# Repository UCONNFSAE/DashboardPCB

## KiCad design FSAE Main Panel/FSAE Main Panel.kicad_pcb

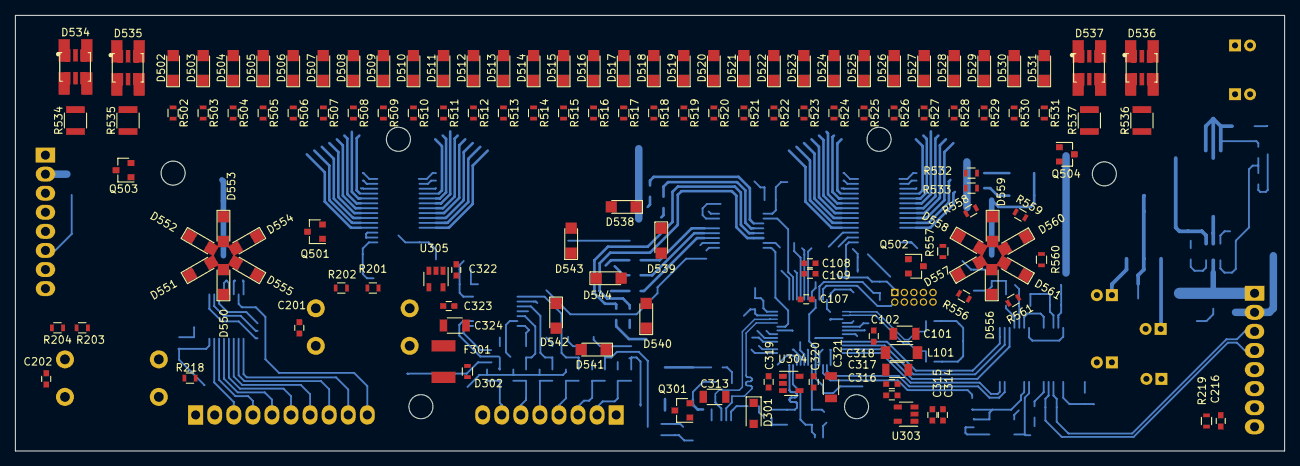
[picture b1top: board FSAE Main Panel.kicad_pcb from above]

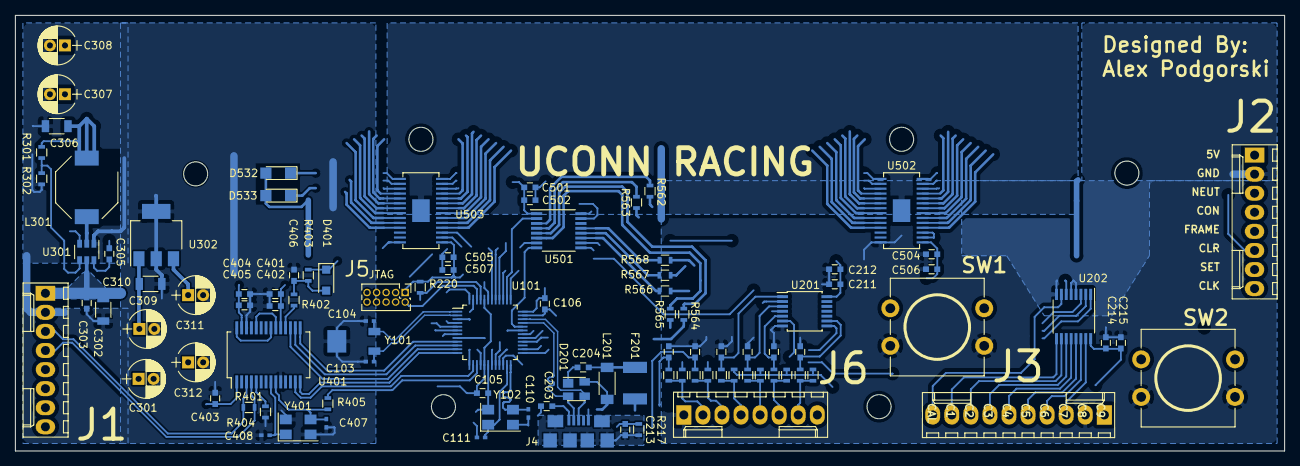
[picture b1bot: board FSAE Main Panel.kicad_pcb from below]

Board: 4 copper layers, 169.0 x 58.0 mm, 232 parts (99 on the bottom side), 183 nets.

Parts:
C101, C313, C318, C321, C324: 10uF; C_1206
C102, C105, C106, C107, C108, C205, C206, C207, C208, C209, C210, C211, C214, C305, C315, C316, C402, C403, C405, C406, C502, C504, C505: 0.1uF; C_0603
C103, C104, C110, C111, C407, C408: 9.1pF; C_0402_NoSilk
C109, C201, C202, C212, C215, C314, C317, C319, C320, C322, C323, C401, C404, C501, C506, C507: 1uF; C_0603
C203, C204, C213, C216, C303: 4700pF; C_0603
C301, C307, C309, C311: 22uF; CP_Radial_D5.0mm_P2.00mm
C302, C306, C310: 2.2uF; C_1206
C308, C312: 100uF; CP_Radial_D5.0mm_P2.00mm
D201: PRTR5V0U2X; SOT-143
D301, D401: D; D_SOD-123F
D302: D_TVS; R_0603
D502, D503, D504, D505, D506, D507, D508, D509, D510, D511, D512, D513, D514, D515, D516, D517: SM1206NPGC-IL; LED_1206
D518, D519, D520, D521, D522, D523, D524, D525, D550, D551, D552, D553, D554, D555: SM1206NYC-IL; LED_1206
D526, D527, D528, D529, D530, D531, D532, D533, D556, D557, D558, D559, D560, D561: SM1206NHC-IL; LED_1206
D534, D535, D536, D537: LCB G6SP-DBFA-4J5L-0-140-R18-Z; LCB_G6SP
D538, D539, D540, D541, D542, D543, D544: SM1206NUWC-IL; LED_1206
F201, F301: MF-MSMF050-2
J1, J2, J6: Conn_01x08; Molex_KK-6410-08_08x2.54mm_Straight
J3: Conn_01x10; Molex_KK-6410-10_10x2.54mm_Straight
J4: USB Micro B; 10118192-0001LF
J5: Cortex_Debug; Pin_Header_Straight_2x05_Pitch1.27mm
L101, L201: BLM41PG471SN1L; L_1806
L301: 3.3uH; L_Bourns-SRU8043
Q301: DMG2305UX-13; SOT-23
Q501, Q502, Q503, Q504: SI2308CDS-T1-GE3; SOT-23
R201, R203, R205, R207, R209, R211, R213, R215, R218, R302, R403, R404: 10k; R_0603
R202, R204, R206, R208, R210, R212, R214, R216: 330; R_0603
R217, R219: 1M; R_0603
R220, R402: 1k; R_0603
R301: 56.2k; R_0603
R401, R502, R503, R504, R505, R506, R507, R508, R509, R510, R511, R512, R513, R514, R515, R516, R517, R518, R519, R520, R521, R522, R523, R524, R525, R526, R527, R528, R529, R530, R531, R532, R533, R556, R557, R558, R559, R560, R561, R562, R563, R564, R565, R566, R567, R568: 120; R_0603
R405: 0; R_0603
R534, R535, R536, R537: 11; R_1210
SW1, SW2: SW_SPST; PTS125
U101: SAMD21G18A-AU; TQFP-48_7x7mm_Pitch0.5mm
U201: CD40106BPWR; TSSOP-14_4.4x5mm_Pitch0.65mm
U202: CD74HC238PWR; TSSOP-16_4.4x5mm_Pitch0.65mm
U301: TPS564201; SOT-23-6
U302: LM2940IMP-5.0/NOPB; SOT-223-3_TabPin2
U303, U304, U305: LP5907MFX-3.3; SOT-23-5
U401: MCP25625; SSOP-28_5.3x10.2mm_Pitch0.65mm
U501: TLC6C598; TSSOP-16_4.4x5mm_Pitch0.65mm
U502, U503: TLC6C5816
Y101: 32.768kHz; MS1V-T1K
Y102, Y401: 16MHz; Crystal_SMD_5032-4pin_5.0x3.2mm

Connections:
+3.3VA: C105.2, C107.1, C316.1, C317.1, C318.1, L101.2, U101.17, U101.44, U303.5
+3V3: C106.1, C211.1, C212.1, C320.1, C321.1, C401.1, C402.1, C403.1, C501.1, C502.1, C504.2, C505.2, C506.1, C507.1, D401.1, J5.1, R201.1, R203.1, R220.1, R403.1, U101.36, U201.14, U202.6, U304.5, U401.1, U401.19, U501.1, U502.1, U503.1
+5V: C311.1, C312.1, C404.1, C405.1, D301.2, Q301.1, U302.3, U401.27
/CAN/X16M_C+: C407.1, R405.1, U401.9, Y401.3
/CAN/X16M_C-: C408.1, U401.8, Y401.1
/Display/B1: D534.1, R534.2
/Display/B2: D535.1, R535.2
/Display/B3: D536.1, R536.2
/Display/B4: D537.1, R537.2
/Display/FRAME_INT1: U501.9, U503.12
/Display/FRAME_INT2: U502.12, U503.15
/Display/G1: D502.1, R502.1
/Display/G2: D503.1, R503.1
/Display/G3: D504.1, R504.1
/Display/G4: D505.1, R505.1
/Display/G5: D506.1, R506.1
/Display/G6: D507.1, R507.1
/Display/G7: D508.1, R508.1
/Display/G8: D509.1, R509.1
/Display/G9: D510.1, R510.1
/Display/G10: D511.1, R511.1
/Display/G11: D512.1, R512.1
/Display/G12: D513.1, R513.1
/Display/G13: D514.1, R514.1
/Display/G14: D515.1, R515.1
/Display/G15: D516.1, R516.1
/Display/G16: D517.1, R517.1
/Display/OP1: D556.1, R556.1
/Display/OP2: D557.1, R557.1
/Display/OP3: D558.1, R558.1
/Display/OP4: D559.1, R559.1
/Display/OP5: D560.1, R560.1
/Display/OP6: D561.1, R561.1
/Display/OP_CONTROL: Q502.3, R556.2, R557.2, R558.2, R559.2, R560.2, R561.2
/Display/R1: D526.1, R526.1
/Display/R2: D527.1, R527.1
/Display/R3: D528.1, R528.1
/Display/R4: D529.1, R529.1
/Display/R5: D530.1, R530.1
/Display/R6: D531.1, R531.1
/Display/R7: D532.1, R532.1
/Display/R8: D533.1, R533.1
/Display/RPM_1: R502.2, U502.4
/Display/RPM_2: R503.2, U502.5
/Display/RPM_3: R504.2, U502.6
/Display/RPM_4: R505.2, U502.7
/Display/RPM_5: R506.2, U502.8
/Display/RPM_6: R507.2, U502.9
/Display/RPM_7: R508.2, U502.10
/Display/RPM_8: R509.2, U502.11
/Display/RPM_9: R510.2, U502.18
/Display/RPM_10: R511.2, U502.19
/Display/RPM_11: R512.2, U502.20
/Display/RPM_12: R513.2, U502.21
/Display/RPM_13: R514.2, U502.22
/Display/RPM_14: R515.2, U502.23
/Display/RPM_15: R516.2, U502.24
/Display/RPM_16: R517.2, U502.25
/Display/RPM_17: R518.2, U503.4
/Display/RPM_18: R519.2, U503.5
/Display/RPM_19: R520.2, U503.6
/Display/RPM_20: R521.2, U503.7
/Display/RPM_21: R522.2, U503.8
/Display/RPM_22: R523.2, U503.9
/Display/RPM_23: R524.2, U503.10
/Display/RPM_24: R525.2, U503.11
/Display/RPM_25: R526.2, U503.18
/Display/RPM_26: R527.2, U503.19
/Display/RPM_27: R528.2, U503.20
/Display/RPM_28: R529.2, U503.21
/Display/RPM_29: R530.2, U503.22
/Display/RPM_30: R531.2, U503.23
/Display/RPM_31: R532.2, U503.24
/Display/RPM_32: R533.2, U503.25
/Display/SFT_1: Q504.3, R536.1, R537.1
/Display/SFT_2: Q503.3, R534.1, R535.1
/Display/Y1: D518.1, R518.1
/Display/Y2: D519.1, R519.1
/Display/Y3: D520.1, R520.1
/Display/Y4: D521.1, R521.1
/Display/Y5: D522.1, R522.1
/Display/Y6: D523.1, R523.1
/Display/Y7: D524.1, R524.1
/Display/Y8: D525.1, R525.1
/Display/a: D538.1, R562.1
/Display/aI: R562.2, U501.3
/Display/b: D539.1, R563.1
/Display/bI: R563.2, U501.4
/Display/c: D540.1, R564.1
/Display/cI: R564.2, U501.5
/Display/d: D541.1, R565.1
/Display/dI: R565.2, U501.6
/Display/e: D542.1, R566.1
/Display/eI: R566.2, U501.11
/Display/f: D543.1, R567.1
/Display/fI: R567.2, U501.12
/Display/g: D544.1, R568.1
/Display/gI: R568.2, U501.13
/External Interface/CAL2: J3.3, U202.15
/External Interface/CAL3: J3.4, U202.14
/External Interface/CAL4: J3.5, U202.13
/External Interface/CAL5: J3.6, U202.12
/External Interface/CAL6: J3.7, U202.11
/External Interface/CAL7: J3.8, U202.10
/External Interface/CAL8: J3.9, U202.9
/External Interface/CAL9: J3.10, U202.7
/External Interface/CAN_SHLD: C216.2, J1.8, R219.1
/External Interface/DSFT_a: J6.3, R207.1, R208.1
/External Interface/SW1_L: C201.1, R202.2, SW1.2
/External Interface/SW2_L: C202.1, R204.2, SW2.2
/External Interface/SWS1_a: J6.4, R209.1, R210.1
/External Interface/SWS1_d: C207.1, R210.2, U201.1
/External Interface/SWS2_a: J6.5, R211.1, R212.1
/External Interface/SWS2_d: C208.1, R212.2, U201.3
/External Interface/SWS3_a: J6.6, R213.1, R214.1
/External Interface/SWS3_d: C209.1, R214.2, U201.5
/External Interface/SWS4_a: J6.7, R215.1, R216.1
/External Interface/SWS4_d: C210.1, R216.2, U201.9
/External Interface/USB_SHLD: C213.1, J4.6, R217.2
/External Interface/USFT_a: J6.2, R205.1, R206.1
/External Interface/VBUS: C203.2, D201.4, J4.1, L201.2
/External Interface/V_USB_1: C204.2, F201.2, L201.1
/Power/+5V_INT: C313.1, C314.1, C315.1, C319.1, C322.1, D301.1, Q301.2, U303.1, U303.3, U304.1, U304.3, U305.1, U305.3
/VCORE1: C108.1, C109.1, U101.43
/VDDANA: C101.1, C102.1, L101.1, U101.6
/X16M+: C111.1, U101.23, Y102.1
/X16M-: C110.1, U101.24, Y102.3
/X32+: C104.2, U101.1, Y101.1
/X32-: C103.2, U101.2, Y101.2
CAL_IN: J3.1, R218.1, U101.22
CAL_a: U101.28, U202.1
CAL_b: U101.29, U202.2
CAL_c: U101.30, U202.3
CAN_CS: U101.11, U401.17
CAN_IN+: J1.4, R401.2, U401.4
CAN_IN-: J1.3, R401.1, U401.3
CAN_INT: U101.14, U401.13
CAN_MISO: U101.10, U401.16
CAN_MOSI: U101.9, U401.15
CAN_SCLK: U101.12, U401.14
CAN_V+: C301.1, C302.1, C303.1, C309.1, C310.1, J1.1, R205.2, R207.2, U301.3, U301.5, U302.1
DSFT: C206.1, J1.6, R208.2
DWC_CONT: J2.4, U101.8
EXT_+3V3: C214.1, C215.1, D302.1, F301.1, R209.2, R211.2, R213.2, R215.2, U202.16
FRAME_CLK: J2.8, U101.37, U501.15, U502.17, U503.17
FRAME_CLR: J2.6, U101.48, U501.7, U502.13, U503.13
FRAME_IN: U101.38, U501.2
FRAME_OUT: J2.5, U502.15
FRAME_SET: J2.7, U101.41, U501.10, U502.16, U503.16
GCLK_0: R405.2, U101.15
GND: C101.2, C102.2, C103.1, C104.1, C105.1, C106.2, C107.2, C108.2, C109.2, C110.2, C111.2, C201.2, C202.2, C203.1, C204.1, C205.2, C206.2, C207.2, C208.2, C209.2, C210.2, C211.2, C212.2, C213.2, C214.2, C215.2, C216.1, C301.2, C302.2, C303.2, C306.2, C307.2, C308.2, C309.2, C310.2, C311.2, C312.2, C313.2, C314.2, C315.2, C316.2, C317.2, C318.2, C319.2, C320.2, C321.2, C322.2, C323.2, C324.2, C401.2, C402.2, C403.2, C404.2, C405.2, C406.2, C407.2, C408.2, C501.2, C502.2, C504.1, C505.1, C506.2, C507.2, D201.1, D302.2, J1.2, J2.2, J3.2, J4.5, J5.3, J5.5, J6.1, Q501.2, Q502.2, Q503.2, Q504.2, R217.1, R218.2, R219.2, R302.2, R404.2, SW1.1, SW2.1, U101.5, U101.18, U101.35, U101.42, U201.7, U202.4, U202.5, U202.8, U301.1, U302.2, U303.2, U304.2, U305.2, U401.10, U401.26, U501.16, U502.28, U503.28, Y101.3, Y102.2, Y102.4, Y401.2, Y401.4
HIGH_TEMP: Q501.1, U101.39
LED_+5V: C306.1, C307.1, C308.1, D502.2, D503.2, D504.2, D505.2, D506.2, D507.2, D508.2, D509.2, D510.2, D511.2, D512.2, D513.2, D514.2, D515.2, D516.2, D517.2, D518.2, D519.2, D520.2, D521.2, D522.2, D523.2, D524.2, D525.2, D526.2, D527.2, D528.2, D529.2, D530.2, D531.2, D532.2, D533.2, D534.2, D535.2, D536.2, D537.2, D538.2, D539.2, D540.2, D541.2, D542.2, D543.2, D544.2, D550.2, D551.2, D552.2, D553.2, D554.2, D555.2, D556.2, D557.2, D558.2, D559.2, D560.2, D561.2, J2.1, L301.1, R301.1
unnamed: C305.1, L301.2, U301.2
unnamed: C305.2, U301.6
unnamed: C323.1, C324.1, F301.2, U305.5
unnamed: C406.1, D401.2, R402.1, R403.2
unnamed: R301.2, R302.1, U301.4
unnamed: R402.2, U401.18
unnamed: R404.1, U401.5
unnamed: U401.20, U401.24
unnamed: U401.21, U401.28
OIL_PRES: Q502.1, U101.7
SHIFT1: Q503.1, U101.3
SHIFT2: Q504.1, U101.4
SWCLK: J5.4, R220.2, U101.45
SWDIO: J5.2, U101.46
SWS1: U101.26, U201.2
SWS2: U101.25, U201.4
SWS3: U101.20, U201.6
SWS4: U101.21, U201.8
USB_D+: D201.3, J4.3, U101.34
USB_D-: D201.2, J4.2, U101.33
USB_POWER: F201.1, Q301.3
USFT: C205.1, J1.5, R206.2
~CLEAR: R203.2, R204.1, U101.19
~NEUT: J1.7, J2.3
~PWM_GREEN: U101.31, U502.2, U502.3
~PWM_RED: U101.16, U503.3
~PWM_WHITE: U101.32, U501.8
~PWM_YELLOW: U101.13, U503.2
~RESET: J5.10, R201.2, R202.1, U101.40
~RPM_EN: U101.47, U502.14, U503.14

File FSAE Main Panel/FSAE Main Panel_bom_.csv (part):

Component,Description,Part,References,Value,Footprint,Quantity Per PCB,Datasheet,Part Number,Sheetpath,Digikey P/N,Manufacturer,Function
1,"Unpolarized capacitor, small symbol",C_Small,C103 C104 C110 C111 C407 C408,9.1pF,C_0402_NoSilk,6,https://api.kemet.com/component-edge/download/datasheet/C040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,C0402C919C5GAC7867,/,399-14287-1-ND,KEMET,
2,Unpolarized capacitor,C,C203 C204 C213 C216 C303,4700pF,C_0603,5,https://api.kemet.com/component-edge/download/specsheet/C060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,C0603C472K5RACAUTO,/External Interface/,399-6896-1-ND,KEMET,
3,"Unpolarized capacitor, small symbol",C_Small,C102 C105 C106 C107 C108 C205 C206 C207 C208 C209 C210 C211 C214 C305 C315 C316 C402 C403 C405 C406 C502 C504 C505,0.1uF,C_0603,23,https://api.kemet.com/component-edge/download/specsheet/C060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,C0603C104K5RACAUTO,/,399-6856-1-ND,KEMET,
4,"Unpolarized capacitor, small symbol",C_Small,C109 C201 C202 C212 C215 C314 C317 C319 C320 C322 C323 C401 C404 C501 C506 C507,1uF,C_0603,16,https://api.kemet.com/component-edge/download/specsheet/C060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,C0603C105K4RACAUTO,/,399-17704-1-ND,KEMET,
5,Unpolarized capacitor,C,C302 C306 C310,2.2uF,C_1206,3,https://api.kemet.com/component-edge/download/specsheet/C120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,C1206C225K5RACAUTO,/Power/,399-7019-1-ND,KEMET,
6,"Unpolarized capacitor, small symbol",C_Small,C101 C313 C318 C321 C324,10uF,C_1206,5,https://api.kemet.com/component-edge/download/datasheet/C120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,C1206C106K4RACAUTO,/,399-7012-1-ND,KEMET,CAP CER 10UF 25V X5R 1206
7,Unpolarized capacitor,C,C301 C307 C309 C311,22uF,CP_Radial_D5.0mm_P2.00mm,4,https://api.kemet.com/component-edge/download/specsheet/ESK2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,ESK226M050AC3AA,/Power/,399-6108-ND,KEMET,
8,Unpolarized capacitor,C,C308 C312,100uF,CP_Radial_D5.0mm_P2.00mm,2,https://api.kemet.com/component-edge/download/datasheet/ESK1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,ESK107M016AC3AA,/Power/,399-6601-ND,KEMET,
9,Diode,D,D301 D401,D,D_SOD-123F,2,https://www.diodes.com/assets/Datasheets/MBR230S1F.pdf,MBR230S1F-7,/Power/,MBR230S1F-7DICT-ND,Diodes Inc,
10,Bidirectional transient-voltage-suppression diode,D_TVS,D302,D_TVS,R_0603,1,https://www.ti.com/lit/ds/symlink/tpd1e10b06.pdf,TPD1E10B06DPYR,/Power/,296-30406-1-ND,TI,
11,"Light emitting diode, small symbol",LED_Small,D534 D535 D536 D537,LCB G6SP-DBFA-4J5L-0-140-R18-Z,LCB_G6SP,4,https://dammedia.osram.info/media/resource/hires/osram-dam-6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,LCB G6SP-DBFA-4J5L-0-140-R18-Z,/Display/,475-3674-1-ND,OSRAM,Shift_1 Shift_2 Shift_3 Shift_4
12,,PRTR5V0U2X,D201,PRTR5V0U2X,SOT-143,1,https://assets.nexperia.com/documents/data-sheet/PRTR5V0U2X.pdf,"PRTR5V0U2X,215",/External Interface/,1727-3884-1-ND,Nexperia,
13,"Light emitting diode, small symbol",LED_Small,D526 D527 D528 D529 D530 D531 D532 D533 D556 D557 D558 D559 D560 D561,SM1206NHC-IL,LED_1206,14,https://www.bivar.com/Portals/0/Products/SM1206NHC-IL.pdf,SM1206NHC-IL,/Display/,492-1944-1-ND,Bivar,12500-Red 13000-Red 13500-Red 14000-Red 14500-Red 15000-Red Spare-Red Oil Pressure
14,"Light emitting diode, small symbol",LED_Small,D502 D503 D504 D505 D506 D507 D508 D509 D510 D511 D512 D513 D514 D515 D516 D517,SM1206NPGC-IL,LED_1206,16,https://www.bivar.com/parts_content/Datasheets/SM1206NPGC-IL.pdf,SM1206NPGC-IL,/Display/,492-1945-1-ND,Bivar,500-Green 1000-Green 1500-Green 2000-Green 2500-Green 3000-Green 3500-Green 4000-Green 4500-Green 5000-Green 5500-Green 6000-Green 6500-Green 7000-Green 7500-Green 8000-Green
15,"Light emitting diode, small symbol",LED_Small,D538 D539 D540 D541 D542 D543 D544,SM1206NUWC-IL,LED_1206,7,https://www.bivar.com/parts_content/Datasheets/SM1206NUWC-IL.pdf,SM1206NUWC-IL,/Display/,492-1946-1-ND,Bivar,7Seg_A 7Seg_B 7Seg_C 7Seg_D 7Seg_E 7Seg_F 7Seg_G
16,"Light emitting diode, small symbol",LED_Small,D518 D519 D520 D521 D522 D523 D524 D525 D550 D551 D552 D553 D554 D555,SM1206NYC-IL,LED_1206,14,https://www.bivar.com/Files/Datasheets/SM1206NYC-IL.pdf,SM1206NYC-IL,/Display/,492-1947-1-ND,Bivar,8500-Yellow 9000-Yellow 9500-Yellow 10000-Yellow 10500-Yellow 11000-Yellow 11500-Yellow 12000-Yellow High Temp
17,"Resettable fuse, polymeric positive temperature coefficient",Polyfuse,F201 F301,MF-MSMF050-2,MF-MSMF050-2,2,https://www.bourns.com/docs/Product-Datasheets/mfmsmf.pdf,MF-MSMF050-2,/External Interface/,IRLML6402PBFCT-ND,Bourns,
18,"Heatsink with electrical connection, 1 pin",Heatsink_Pad,HS1 HS2,Heatsink_Pad,PinHeader_1x01_P2.54mm_Vertical,2,~,,/Display/,,,
19,"Generic connector, single row, 01x08, script generated (kicad-library-utils/schlib/autogen/connector/)",Conn_01x08,J1 J2 J6,Conn_01x08,Molex_KK-6410-08_08x2.54mm_Straight,3,"https://media.digikey.com/pdf/Data%20Sheets/Molex%20PDFs/171856,57_Brief.pdf",1718571008,/External Interface/,WM10303-ND,Molex,
20,"Generic connector, single row, 01x10, script generated (kicad-library-utils/schlib/autogen/connector/)",Conn_01x10,J3,Conn_01x10,Molex_KK-6410-10_10x2.54mm_Straight,1,"https://media.digikey.com/pdf/Data%20Sheets/Molex%20PDFs/171856,57_Brief.pdf",0022122104,/External Interface/,WM2719-ND,Molex,
21,,Cortex_Debug,J5,Cortex_Debug,Pin_Header_Straight_2x05_Pitch1.27mm,1,https://cdn.amphenol-icc.com/media/wysiwyg/files/drawing/200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,20021111-00010T4LF,/External Interface/,609-3712-ND,Amphenol,
22,,Conn_01x06-conn,J4,USB Micro B,10118192-0001LF,1,https://www.amphenol-icc.com/media/wysiwyg/files/drawing/101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,10118192-0001LF,/External Interface/,609-4613-1-ND,Amphenol,
23,Inductor,L,L301,3.3uH,L_Bourns-SRU8043,1,https://www.bourns.com/docs/Product-Datasheets/SRR1050A.pdf,SRR1050A-3R3Y,/Power/,SRR1050A-3R3YCT-ND,Bourns,
24,"Ferrite bead, small symbol",Ferrite_Bead_Small,L101,BLM41PG471SN1L,L_1806,1,https://www.murata.com/en-us/products/productdata/8796739862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,BLM41PG471SN1L,/,490-1060-1-ND,Murata,
25,Ferrite bead,Ferrite_Bead,L201,BLM41PG471SN1L,L_1806,1,https://www.murata.com/en-us/products/productdata/8796739862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,BLM41PG471SN1L,/External Interface/,490-1060-1-ND,Murata,
26,"P-MOSFET transistor, gate/source/drain",Q_PMOS_GSD,Q301,DMG2305UX-13,SOT-23,1,https://www.diodes.com/assets/Datasheets/DMG2305UX.pdf,DMG2305UX-13,/Power/,DMG2305UX-13DICT-ND,Diodes Inc,
27,"N-MOSFET transistor, gate/source/drain",Q_NMOS_GSD,Q501 Q502 Q503 Q504,SI2308CDS-T1-GE3,SOT-23,4,http://www.vishay.com/docs/77744/si2308cds.pdf,SI2308CDS-T1-GE3,/Display/,SI2308CDS-T1-GE3CT-ND,Vishay,
28,Resistor,R,R405,0,R_0603,1,https://www.seielect.com/catalog/sei-rmcf_rmcp.pdf,RMCF0603ZT0R00,/CAN/,RMCF0603ZT0R00CT-ND,Stackpole,
29,"Resistor, small symbol",R_Small,R534 R535 R536 R537,11,R_1210,4,http://www.vishay.com/docs/20035/dcrcwe3.pdf,CRCW121011R0FKEA,/Display/,541-11.0AACT-ND,Vishay,
30,Resistor,R,R401 R502 R503 R504 R505 R506 R507 R508 R509 R510 R511 R512 R513 R514 R515 R516 R517 R518 R519 R520 R521 R522 R523 R524 R525 R526 R527 R528 R529 R530 R531 R532 R533 R550 R551 R552 R553 R554 R555 R556 R557 R558 R559 R560 R561 R562 R563 R564 R565 R566 R567 R568,120,R_0603,52,https://www.seielect.com/catalog/sei-rmcf_rmcp.pdf,RMCF0603FT120R,/CAN/,RMCF0603FT120RCT-ND,Stackpole,
31,Resistor,R,R202 R204 R206 R208 R210 R212 R214 R216,330,R_0603,8,https://www.seielect.com/catalog/sei-rmcf_rmcp.pdf,RMCF0603JT330R,/External Interface/,RMCF0603JT330RCT-ND,Stackpole,
32,Resistor,R,R220 R402,1k,R_0603,2,https://www.seielect.com/catalog/sei-rmcf_rmcp.pdf,RMCF0603JT1K00,/External Interface/,RMCF0603JT1K00CT-ND,Stackpole,
33,Resistor,R,R201 R203 R205 R207 R209 R211 R213 R215 R218 R302 R403 R404,10k,R_0603,12,https://www.seielect.com/catalog/sei-rmcf_rmcp.pdf,RMCF0603JT10K0,/External Interface/,RMCF0603JT10K0CT-ND,Stackpole,
34,Resistor,R,R301,56.2k,R_0603,1,https://www.seielect.com/catalog/sei-rmcf_rmcp.pdf,RMCF0603FT56K2,/Power/,RMCF0603FT56K2CT-ND,Stackpole,
35,"Resistor, small symbol",R_Small,R217 R219,1M,R_0603,2,https://www.seielect.com/catalog/sei-rmcf_rmcp.pdf,RMCF0603JT1M00,/External Interface/,RMCF0603JT1M00CT-ND,Stackpole,
36,"Push button switch, generic, two pins",SW_Push,SW1 SW2,SW_SPST,PTS125,2,https://dznh3ojzb2azq.cloudfront.net/products/Tactile/PTS125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,PTS125SK43-2 LFS,/External Interface/,CKN9139-ND,C&K,
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
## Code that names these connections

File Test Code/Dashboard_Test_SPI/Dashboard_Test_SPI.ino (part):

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#include "wiring_private.h"
#include <mcp_can.h>

#define FRAME_IN 2
#define FRAME_CLK 5
#define GEAR_CLR 6
#define GEAR_SET 10

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#define LED_MOSI  2

/*
 * CAN_MOSI / Arduino Pin A3 / PA4
 * CAN_MISO / Arduino Pin A4 / PA5
 * CAN_SCK  / Arduino Pin 9  / PA7
 * CAN_CS   / Arduino Pin 8  / PA6
 */

#define CAN_MISO  18
#define CAN_SCK   9
#define CAN_MOSI  17
#define CAN_CS    8

// Override default SPI settings
SPISettings SHIFT(2000000, MSBFIRST, SPI_MODE0);
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  //SerialUSB.begin(115200);
  //while(!SerialUSB);

  pinMode(CAN_CS, OUTPUT);
  digitalWrite(CAN_CS, HIGH);
  
  //HIGH TEMP
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  PORT->Group[PORTB].DIRSET.reg = PORT_PB11;      // Set pin as output
  PORT->Group[PORTB].OUTCLR.reg = PORT_PB11;      // Set pin to low

  pinMode(FRAME_IN, OUTPUT);
  pinMode(FRAME_CLK, OUTPUT);
  pinMode(GEAR_SET, OUTPUT);
  pinMode(GEAR_CLR, OUTPUT);

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
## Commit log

2018-10-23 Added TE Connetor
2018-10-23 Test Pin Change
2018-10-23 Wires to TE connector
2018-10-24 Libraries used for PCB
2018-10-24 Power circuit to MCU
2018-10-24 Sheet Hierarchy
2018-10-31 Hierarchy sheet for Power (WIP)
2018-11-07 Added CAN components
2018-11-10 Added Gear Shift LED display
    Included Gear shift LED 7 segment, resistor array, and shift register driver.
    Gary you'll need to re-add the custom library's youre using because they didn't get pushed to GitHub so KiCad ignored them when the project loaded without them. Components are still there, just until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
2018-11-10 Attempt to fix custom library pathing
2018-11-12 Initial PCB layout
    Started PCB layout with major dimensions.
    Added RPM LEDs.
    Rearranged the file structure for the librarys and the search paths.
2018-11-12 Added RPM LED Control
2018-11-14 Added Blue shift LEDs and proper resistor arrays
2018-11-16 Finished most LEDs, begun power regulators
2018-11-19 Moved USB connection to External_Interface
2018-11-25 Updated power circuit for MCU, used small components on main sheet
2018-11-28 Cortex debugger, GPIO pinning, minor fixes
2018-12-03 Added power regulator for LEDs, further GPIO considerations
2018-12-27 Updated to KiCad 5
2019-01-06 Updated Footprint Association
2019-01-09 New footprints, finished associating footprints
2019-01-12 Edited footprints, started PCB layout
2019-01-19 Placed LEDs on PCB
2019-01-21 Added Warning Lights
    Added Warning lights and started bulk routing
2019-01-27 Updated PCB
2019-02-20 Added warning nMOS circuit, simulated, updated PCB
2019-03-02 Major Revision
    Deleted a ton of routes, Sorry Gary.
    Changed all LEDs to 1206s for better brightness
    Added a lot of local net names for easier routing
    Flipped J203 for better routing
    Expanded board outline to fit final dashboard cutout
    Added half of the Mounting Holes
2019-03-04 Power Supply Changes Again
    Shrunk some 5V layout by switching LM7805's for their SOT223 packages but with very careful top copper considerations for thermal management.
    Shrunk the Right side by 12mm for more clearance near ignition button.
    Fixed Shift Register clock signal routing.
    Changed shift order to be 7 segment first for easiler routing.
    Added Mounting Holes.
    TODO: Figure out Top layer 7 segment placement.
2019-03-04 Minor Routing changes
2019-03-09 More Routing
    Fixed Tactile Switch Footprints
    More routing
2019-03-12 Plotted schematic PDF file
2019-03-13 Most Signal Routing
    Todo: Figure out 7 segment LED placements and route their power traces
2019-03-16 Version 1
2019-03-20 Initial Fabrication
2019-03-28 Manufacturing Tweaks
2019-03-31 Updated attributes and BOM
    Standardized the component attributes and BOM.
    Some errors were identified and will be corrected in the next board revision
2019-04-03 TLC6C5816 test code on SAMD21
    Sends data and PWM signals to TLC6C5816 using SAMD21 in arduino
2019-04-03 TLC6C5816 test code on Arduino Uno
2019-04-03 Added comment block
2019-04-06 Schematic PDF, minor fixes in PCB, test code
2019-04-06 Dashboard test code
2019-04-06 Successfully tested CAN Bus SPI on the Dashboard PCB
2019-04-07 Updated dashboard test code
2019-04-10 Fixed PWM output, figuring frame data
2019-04-11 Dashboard LED through SPI
2019-04-17 Upload test code for CAN bus and clock output
2019-04-20 Warning Panel Test Code
2019-04-20 Warning Panel I2C testing
2019-04-22 Further testing of CAN BUS and I2C LED Driver
2019-04-22 Working CAN BUS code
2019-04-23 Added CAN BUS to SPI test
2019-04-24 Further LED testing and added gear position from CAN
2019-04-25 Working gear indicator
2019-04-26 Working Gear on display, properly reading rpm, eop and ect
2019-04-28 Added RPM logic
2019-04-28 Blue shift lights on an interval earlier
2019-05-05 Forgot to call startup animation
2019-05-28 Added Master Caution logic
2019-09-14 Added oil pressure vs RPM logic
2019-09-14 placeholder
2019-09-14 Custom Variant file required for dashboard code
    Found in *\AppData\Local\Arduino15\packages\SparkFun\hardware\samd\1.5.4\variants
2020-08-07 Updating Schematic
2020-10-10 CAL Switch Input
    Added Cal Switch input Decoder
2020-10-10 Completed V1 of Power Section
    Completed Power Section 5V and 3.3V Regulators
2020-10-18 Completed Circuit and BOM
    First finished draft of circuit design
    Completed BOM
    Footprints assigned
2020-10-19 Netlist Generation
    Tweaks and netlist generation for routing
2020-10-20 LED Layout
    LED placement and initial routing
2020-10-25 Changed Display Power Reg
    Swapped costly complex 5V Rail reg for smaller lower efficiency TPS564201
2020-11-02 Power Supply Layout
    Finished 5V power supply.
    Positioned DWC and Input Connectors
    Completed CAL connector
    Completed Clear Switch
2020-11-07 Complete External IO
    All Connectors placed and wired
    Buttons placed and wired
    External 3.3V regulator complete
    Cal Input IC Complete
2020-11-09 Completed IO and CAN
    Remaining: MCU pinning and changing the 3.3V supply locations
2020-11-10 Reworked board Size
    Made board slightly bigger to fit all MCU breakout in two layer
2020-11-10 Final IO
    Rough Breakout for MCU
    Remaining Signals for assignment:
    CAL_a, CAL_b, CAL_c, CLEAR, DWC_CONT, HIGH_TEMP, FRAME_CLK, FRAME_SET, PWM_WHITE, FRAME_IN, PWM_RED, PWM_YELLOW, PWM_GREEN
2021-01-24 Four Layer Shrink
    Shifted edge connectors and associated components up to reduce board width for clearance issues.
    Changed to four layer board for huge improvement on routing power and ground planes
2021-02-07 Ready for Review
    Completed Routing
2021-02-16 Release Candidate 1
    Review for Manufacture
2021-02-19 Updated Blue LED Pad
    Ambiguity on Blue LED Anode
2022-10-08 Hierarchical Sheets
    Changed to Hierarchical Sheets structure and redid a few little details.
